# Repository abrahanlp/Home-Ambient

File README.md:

# Home-Ambient
 2-wire smart home thermostat with temperature, humidity, pressure and air quality measurements.

The main target is replace traditional tow wires bimetal thermostats with an intelligent one, cable to integrate with [HomeAssistance](https://www.home-assistant.io/) or works _standalone_ with custom firmware.

## 2-wire classical thermostat replacement

### Working principle
Images below explain graphically how this system works.

The main and mandatory system requirement is a big difference between Control an Load level power. While load is some orders of magnitud above, there should not be problem, but is mandatory review every case.

# Product Requirements

| Requirement   | Description  | Definition |
|:-------------:|:-------------|:----------:|
| Temperature	|  Temperature measurement, with minimal interference from the device.	| ±2°C 	|
| Humidity	| Humidity measurement from ambient 	| ±5% 	|
| Air quality	| Air quality estimation by particle detection| Not defined, optional |
| Switch	| 2 pole switch	| >=10A	|
| Switch feedback	| Switch feedback to check operation | Digital or analog |
| HA | Home Assistance integration	| Mandatory	|
| Display | Optional e-Ink display	| No power relevant|
| Autonomy | Capable to operate without power	| At least 2h |

## Hardware architecture
Home-Ambient block diagram is show on image below.

The PCB hardware distribution is proposed on next image.

### Power supply, SEPIC converter
Energy when the load is activated is provided by a battery. The voltage from this power source varies from above and below 3,3V, so it is neccesary _'boost'_ and _'buck'_ converter.
Here is where the SEPIC converter comes to action, capable of manage both situations at the same time.

### CPU
The easiest way to integrate custom electronics on _HomeAssistant_ are the [ESPHome](https://esphome.io/) devices. This smart thermostat will be designed around classical [ESP32-C3](https://www.espressif.com/en/products/socs/esp32-c3).

### Sensors and actuators
The BME680 air quality sensor covers all requirements. More info about this component can be found on [Bosch official website](https://www.bosch-sensortec.com/en/products/environmental-sensors/gas-sensors/bme680).

## Home Assistant integration
As said before, integration is done by [ESPHome](https://esphome.io/), there is no easier way to do this.

After integration on Home-Assistant, a schedule programmer is implemented using the [Niels Faber](https://github.com/nielsfaber) tools.

# More info on [FaultyProject](https://faultyproject.es/)
If you are interested how this project was developed take a look on the next links:
 1. [Introduction](https://faultyproject.es/proyectos/home-ambient/home-ambient-intro/)
 2. [Prototype](https://faultyproject.es/proyectos/home-ambient/home-ambient-prototipo/)
 3. [Schematichs & PCB Design](https://faultyproject.es/proyectos/home-ambient/home-ambient-hardware-esquema-y-pcb/)
 4. [Home Assistant Integration](https://faultyproject.es/proyectos/home-ambient/home-ambient-integracion-con-home-assistant-y-esphome/)
 5. Case design (Future work... )

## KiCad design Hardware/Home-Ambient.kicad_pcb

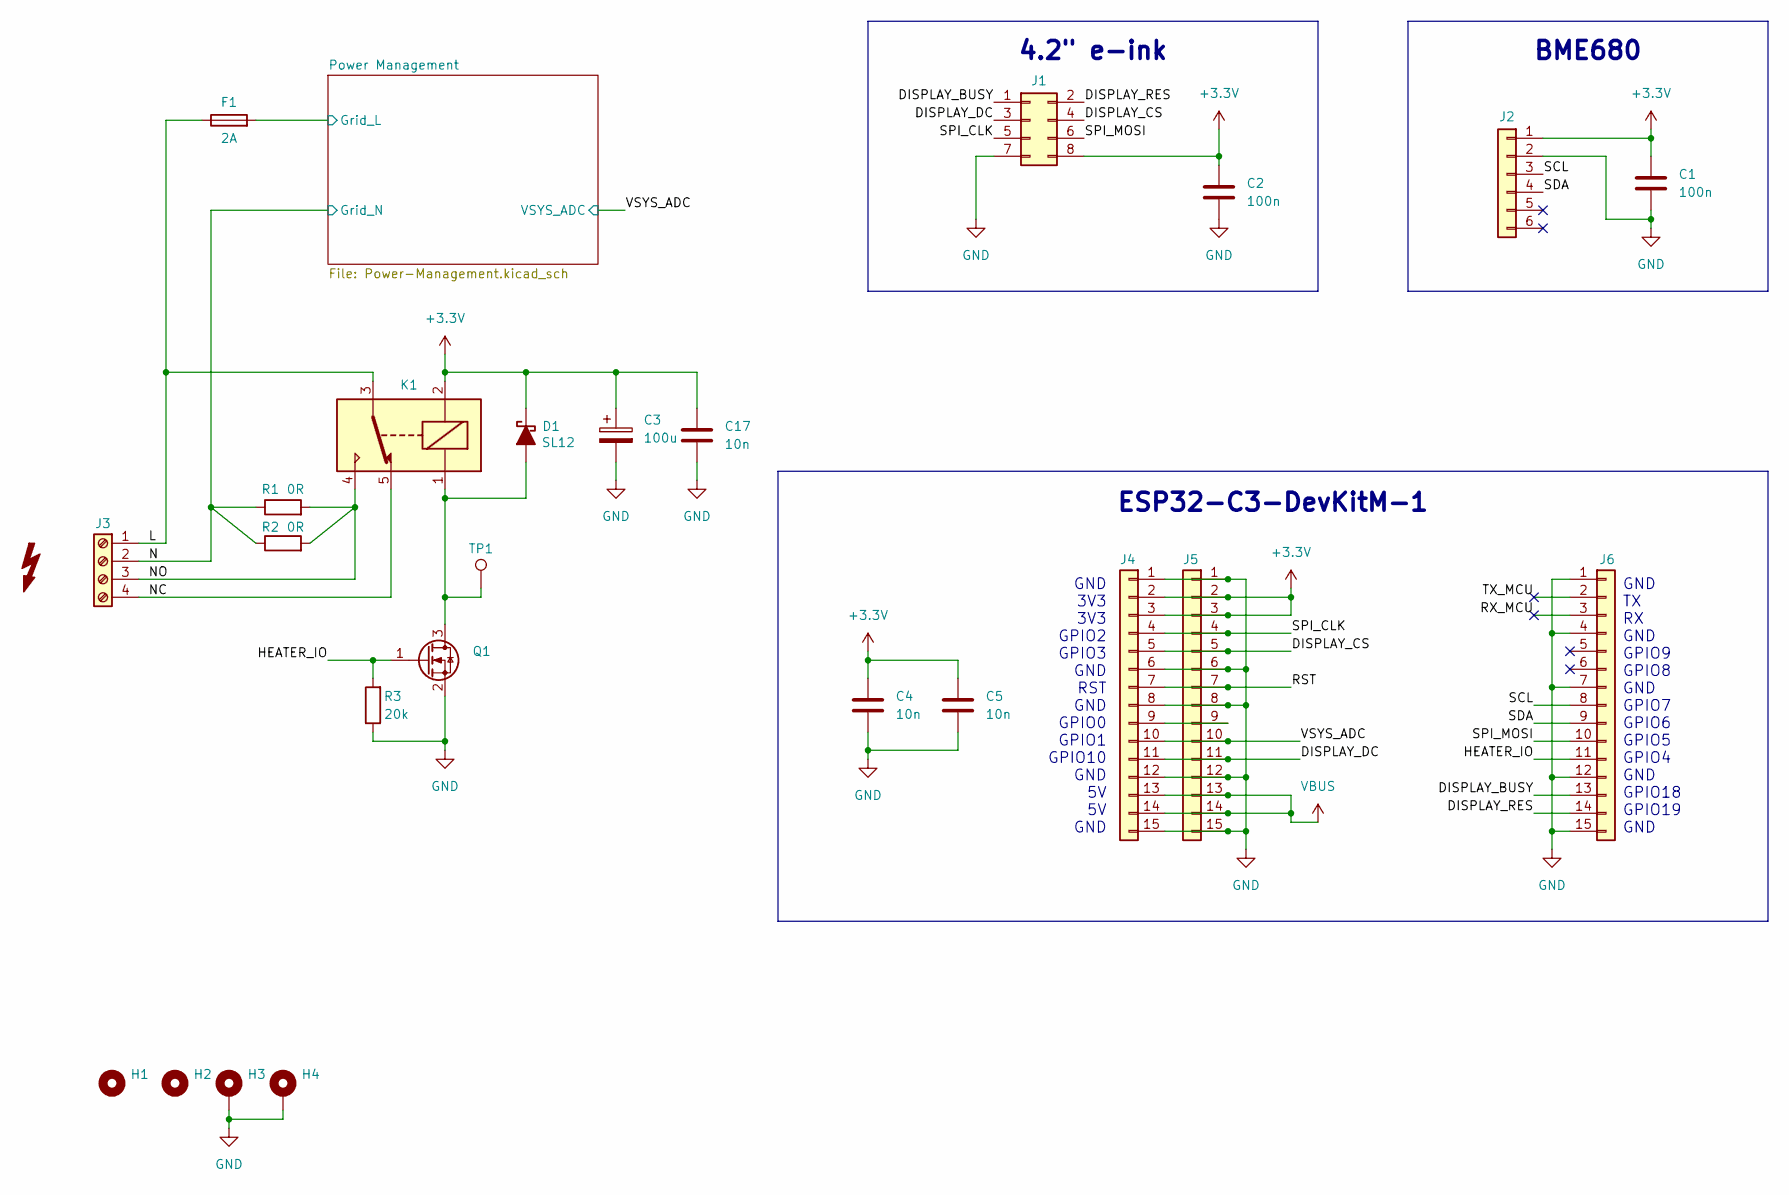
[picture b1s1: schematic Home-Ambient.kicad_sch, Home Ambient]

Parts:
C1, C2: 100n; C_1206_3216Metric_Pad1.33x1.80mm_HandSolder
C3: 100u; C_1210_3225Metric_Pad1.33x2.70mm_HandSolder
C4, C5, C17: 10n; C_1206_3216Metric_Pad1.33x1.80mm_HandSolder
D1: SL12; D_SMA_Handsoldering
F1: 2A; 0697H____
H1, H2: MountingHole; MountingHole_3.2mm_M3
H3, H4: MountingHole_Pad; MountingHole_3.2mm_M3_Pad_TopBottom
J1: Conn_02x05_Odd_Even; PinHeader_2x04_P2.54mm_Vertical
J2: Conn_01x06; PinHeader_1x06_P2.54mm_Vertical
J3: Screw_Terminal_01x04; TerminalBlock_Altech_AK300-4_P5.00mm
J4, J5, J6: Conn_01x15; PinHeader_1x15_P2.54mm_Vertical
K1: Relay_SPDT; J1071CS3VDC36
Q1: SSF2320Y; SOT-23_Handsoldering
R1, R2: 0R; R_1812_4532Metric_Pad1.30x3.40mm_HandSolder
R3: 20k; R_0805_2012Metric_Pad1.20x1.40mm_HandSolder
TP1: TestPoint_Pad_2.0x2.0mm

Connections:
+3.3V: C1.1, C2.1, C3.1, C4.1, C5.1, C17.1, D1.1 (K), J1.8, J2.1, J4.2, J4.3, J5.2, J5.3, K1.2; also elsewhere on the board
/DISPLAY_BUSY: J1.1, J6.13
/DISPLAY_CS: J1.4, J4.5, J5.5
/DISPLAY_DC: J1.3, J4.11, J5.11
/DISPLAY_RES: J1.2, J6.14
/HEATER_IO: J6.11, Q1.1 (G), R3.2
/L: F1.1, J3.1, K1.3
/N: J3.2, R1.1, R2.1; also elsewhere on the board
/NC: J3.4, K1.5
/NO: J3.3, K1.4, R1.2, R2.2
/Power Management/Grid_L: F1.2; also elsewhere on the board
/RST: J4.7, J5.7
/RX_MCU: J6.3
/SCL: J2.3, J6.8
/SDA: J2.4, J6.9
/SPI_CLK: J1.5, J4.4, J5.4
/SPI_MOSI: J1.6, J6.10
/TX_MCU: J6.2
/VSYS_ADC: J4.10, J5.10; also elsewhere on the board
GND: C1.2, C2.2, C3.2, C4.2, C5.2, C17.2, H3.1, H4.1, J1.7, J2.2, J4.1, J4.6, J4.8, J4.12, J4.15, J5.1, J5.6, J5.8, J5.12, J5.15, J6.1, J6.4, J6.7, J6.12, J6.15, Q1.2 (S), R3.1; also elsewhere on the board
unnamed: D1.2 (A), K1.1, Q1.3 (D), TP1.1
unnamed: J4.9, J5.9
VBUS: J4.13, J4.14, J5.13, J5.14

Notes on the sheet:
BME680
4.2" e-ink
GND TX RX GND GPIO9 GPIO8 GND GPIO7 GPIO6 GPIO5 GPIO4 GND GPIO18 GPIO19 GND
GND 3V3 3V3 GPIO2 GPIO3 GND RST GND GPIO0 GPIO1 GPIO10 GND 5V 5V GND
ESP32-C3-DevKitM-1

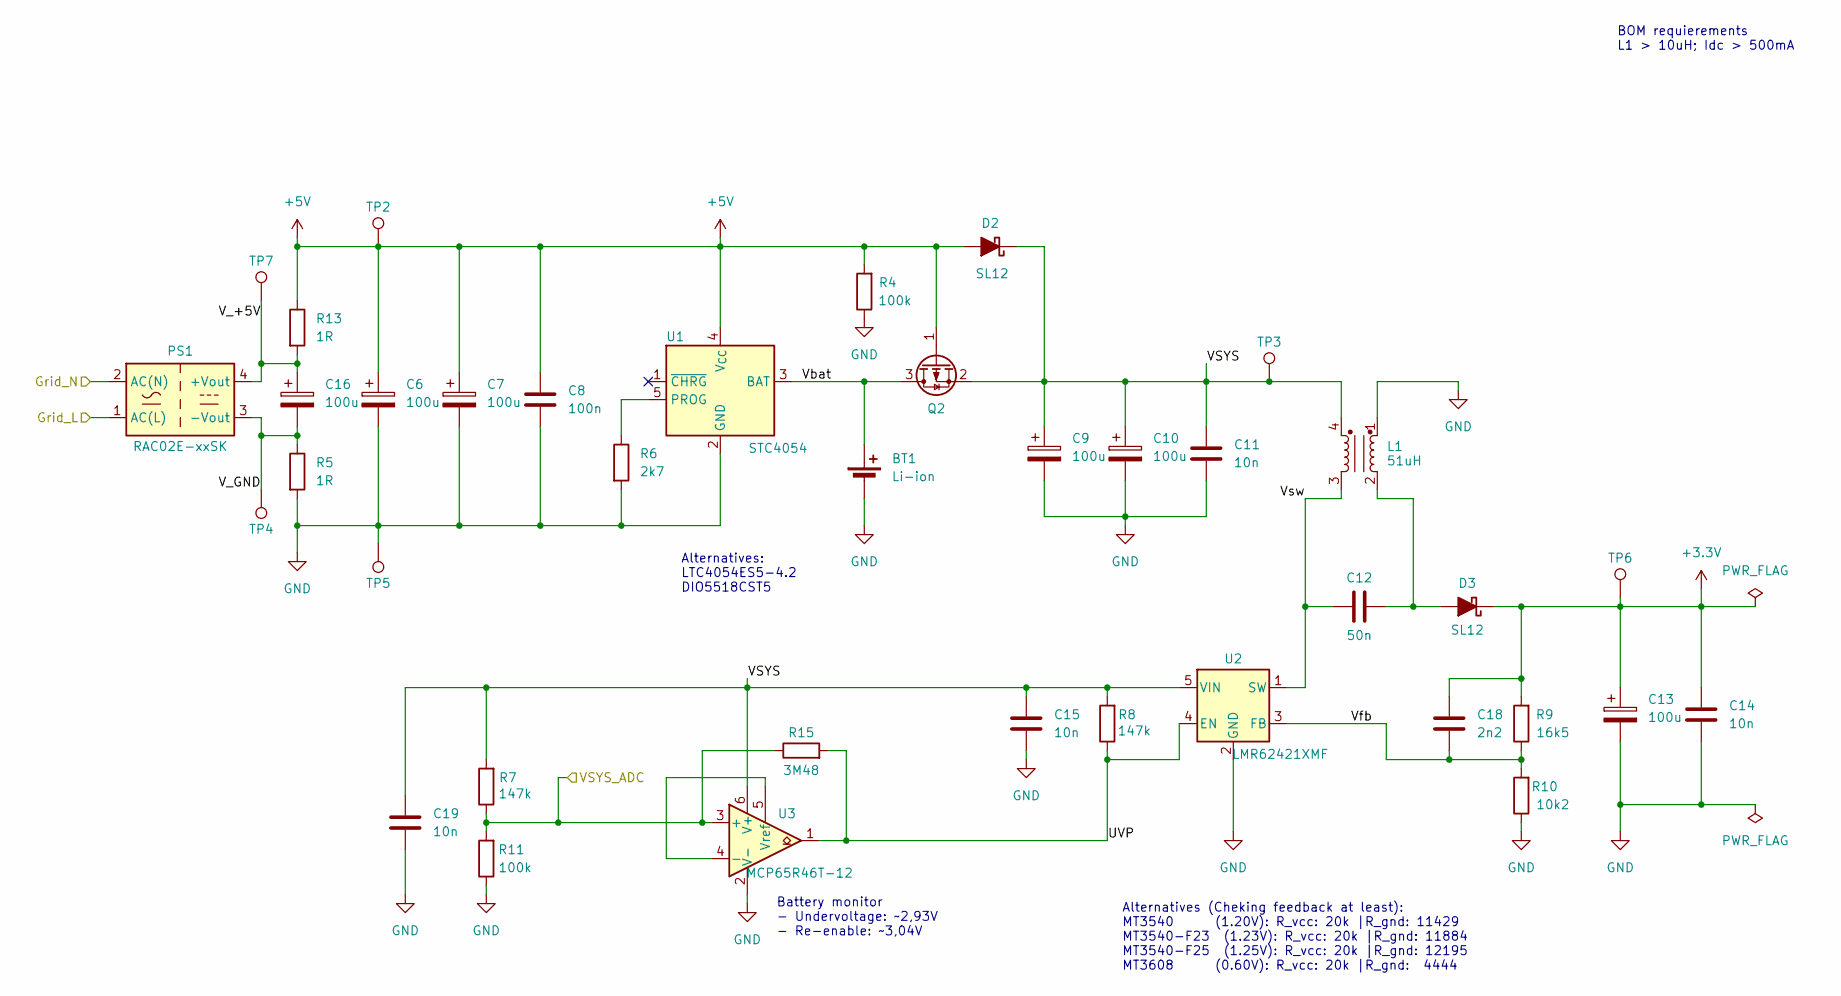
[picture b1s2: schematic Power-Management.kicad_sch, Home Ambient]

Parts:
BT1: Li-ion; Molex_SL_171971-0002_1x02_P2.54mm_Vertical
C6, C7, C9, C10, C13, C16: 100u; C_1210_3225Metric_Pad1.33x2.70mm_HandSolder
C8: 100n; C_1206_3216Metric_Pad1.33x1.80mm_HandSolder
C11, C14, C15, C19: 10n; C_1206_3216Metric_Pad1.33x1.80mm_HandSolder
C12: 50n; C_1206_3216Metric_Pad1.33x1.80mm_HandSolder
C18: 2n2; C_0805_2012Metric_Pad1.18x1.45mm_HandSolder
D2, D3: SL12; D_SMA_Handsoldering
L1: 51uH; Murata_5000A
PS1: RAC02E-xxSK; RAC02E-K
Q2: DMP31D1U-7; SOT-23_Handsoldering
R4, R11: 100k; R_0805_2012Metric_Pad1.20x1.40mm_HandSolder
R5, R13: 1R; R_1206_3216Metric_Pad1.30x1.75mm_HandSolder
R6: 2k7; R_0805_2012Metric_Pad1.20x1.40mm_HandSolder
R7, R8: 147k; R_0805_2012Metric_Pad1.20x1.40mm_HandSolder
R9: 16k5; R_0805_2012Metric_Pad1.20x1.40mm_HandSolder
R10: 10k2; R_0805_2012Metric_Pad1.20x1.40mm_HandSolder
R15: 3M48; R_0805_2012Metric_Pad1.20x1.40mm_HandSolder
TP2, TP3, TP4, TP5, TP6, TP7: TestPoint_Pad_2.0x2.0mm
U1: STC4054; TSOT-23-5_HandSoldering
U2: LMR62421XMF; SOT-23-5_HandSoldering
U3: MCP65R46T-12; SOT-23-6_Handsoldering

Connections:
+3.3V: C13.1, C14.1, C18.1, D3.1 (K), R9.2, TP6.1; also elsewhere on the board
+5V: C6.1, C7.1, C8.1, D2.2 (A), Q2.1 (G), R4.2, R13.1, TP2.1, U1.4 (V_{CC})
/N: PS1.2 (AC(N)); also elsewhere on the board
/Power Management/Grid_L: PS1.1 (AC(L)); also elsewhere on the board
/Power Management/UVP: R8.1, R15.2, U2.4 (EN), U3.1
/Power Management/VSYS: C9.1, C10.1, C11.1, C15.1, C19.1, D2.1 (K), L1.4, Q2.2 (S), R7.2, R8.2, TP3.1, U2.5 (VIN), U3.6 (V+)
/Power Management/V_+5V: C16.1, PS1.4 (+Vout), R13.2, TP7.1
/Power Management/V_GND: C16.2, PS1.3 (-Vout), R5.1, TP4.1
/Power Management/Vbat: BT1.1 (+), Q2.3 (D), U1.3 (BAT)
/Power Management/Vfb: C18.2, R9.1, R10.2, U2.3 (FB)
/Power Management/Vsw: C12.1, L1.3, U2.1 (SW)
/VSYS_ADC: R7.1, R11.2, R15.1, U3.3 (+); also elsewhere on the board
GND: BT1.2 (-), C6.2, C7.2, C8.2, C9.2, C10.2, C11.2, C13.2, C14.2, C15.2, C19.2, L1.1, R4.1, R5.2, R6.2, R10.1, R11.1, TP5.1, U1.2 (GND), U2.2 (GND), U3.2 (V-); also elsewhere on the board
unnamed: C12.2, D3.2 (A), L1.2
unnamed: R6.1, U1.5 (PROG)
unnamed: U3.4 (-), U3.5 (Vref)

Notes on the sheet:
Battery monitor - Undervoltage: ~2,93V - Re-enable: ~3,04V
Alternatives: LTC4054ES5-4.2 DIO5518CST5
Alternatives (Cheking feedback at least): MT3540 (1.20V): R_vcc: 20k |R_gnd: 11429 MT3540-F23 (1.23V): R_vcc: 20k |R_gnd: 11884 MT3540-F25 (1.25V): R_vcc: 20k |R_gnd: 12195 MT3608 (0.60V): R_vcc: 20k |R_gnd: 4444
BOM requierements L1 > 10uH; Idc > 500mA

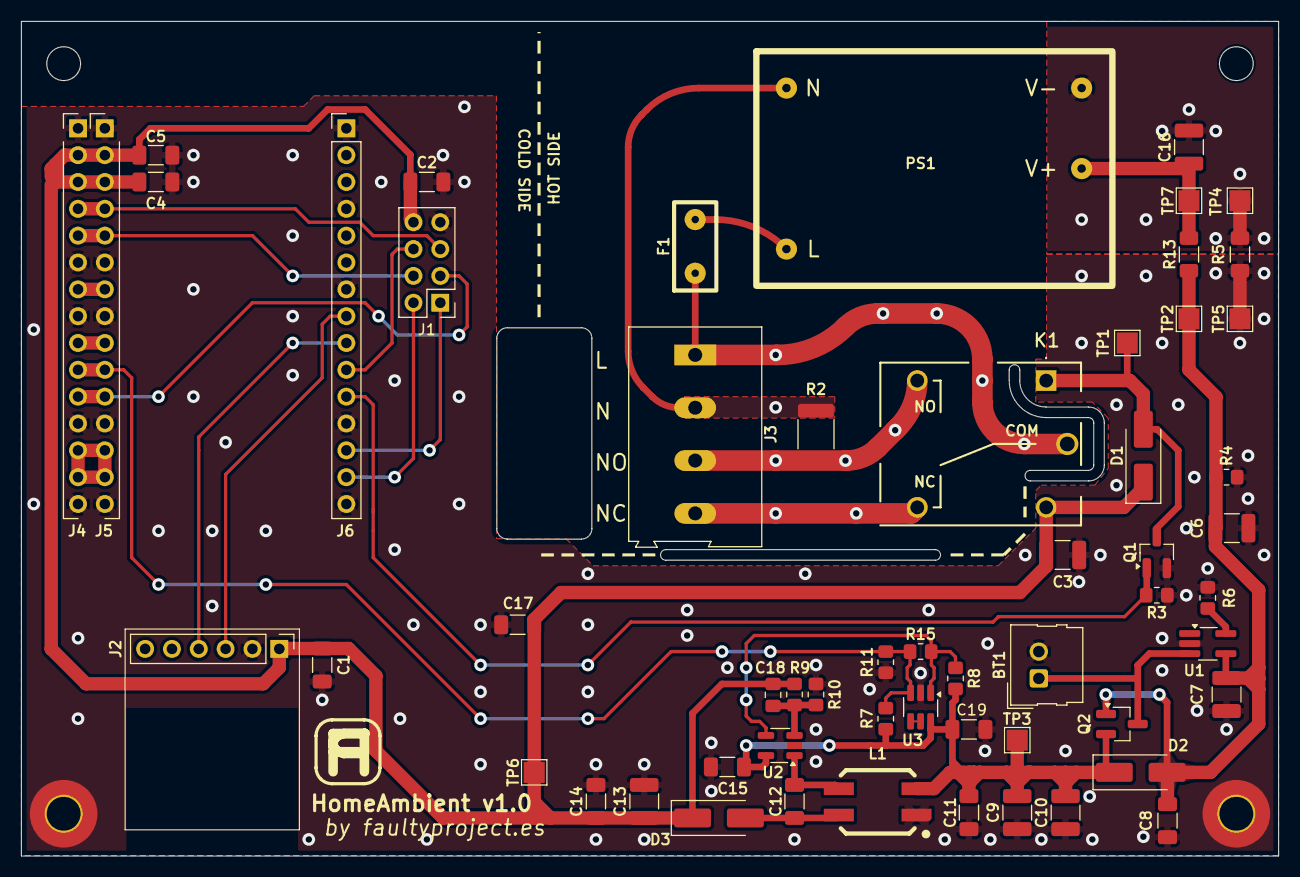
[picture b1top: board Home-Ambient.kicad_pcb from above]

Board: 2 copper layers, 119.0 x 79.0 mm, 62 parts (1 on the bottom side), 32 nets.

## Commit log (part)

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2024-09-13 More project info on README
2024-11-23 Basic Arduino hardware test
2024-12-19 Added YAML ESPHome file.
2025-01-03 Diagram added
2025-04-06 HW to KiCAD 9. Added library components
2025-04-14 RECOM footprint. Pinhead footprints.
2025-04-16 Updated sch.
2025-04-18 SEPIC script Octave.
2025-04-19 Basic SEPIC circuit for calculations. Li-ion charger.
2025-04-30 Basic SEPIC calculations.
2025-05-02 SEPIC first components value approach. SEPIC calculations corrections.
2025-05-03 FP Sheet. Voltage feedback and undervoltage detection.
2025-05-03 ESP32 connections
2025-05-04 Fixed R1 and R2 uv calculation. Current measure resistor en GND power source.
2025-05-30 Complete schematics
2025-05-31 Common mode inductor symbol, footprint
2025-06-01 Common mode footprint pin fix and silkscreen
2025-06-01 Symbol, footprint and 3D model relay
2025-06-03 BOM completed
2025-06-05 Added optional power source
2025-06-12 ZP05SXX00WB footprint
2025-06-15 Fuse and main connector footprints. ERC check.
2025-07-03 Moved SEPIC controller supply from battery to power commuter.
2025-07-04 PCB progress
2025-07-06 New 100uF capacitor package.
2025-07-20 PCB delimitation. Optional 5V Power supply removed because size constraint.
2025-08-07 Mounting holes and PCB progress.
2025-08-08 Fixed references. Parallel resistor on thermostat connection config.
2025-08-10 Equalizing output power supply impedance.
2025-08-10 PCB Progress.
2025-08-12 Grounding pending. DRU file added.
2025-08-13 Ground planes
2025-08-13 Crossing tracks on 90 degrees. Rework on Grid Power tracks
2025-08-13 Replaced main and battery supply switch transistor reference.
2025-08-13 First PCB draft finished.
2025-08-13 Vias placing. 10nF added on 3V relay PDN
2025-08-13 Vias refinement.
2025-08-13 Warning and instrucction silkscreens.
2025-08-14 Add and set 3D models.
2025-08-15 Basic 3D files.
2025-08-16 Added PCB dimmensions
2025-08-16 Case progress
2025-08-17 Enclosure main parts finished.
2025-08-17 Removed soldermask over power tracks. Relay footprint edit for silkscreen margin.
2025-08-29 BOM updated, SEPIC regulator replaced.
2025-08-29 SEPIC footprint fixed.
2025-09-02 Added battery undervoltage circuit.
2025-09-04 Comparator simulation
2025-09-06 Schematic and BOM updated with new undervoltage protection.
2025-09-07 Closed PCB layout
2025-09-07 Check DRU
2025-09-14 Docu diagram update
2025-09-17 Final BOM
2025-09-21 Production files
2025-09-28 Documentation
2025-11-12 Docu update. GPIO0 ADC removed on yaml file
2025-11-25 Voltage system gain and unit update.
2026-01-09 Bottom case
2026-01-11 Basic case
2026-01-11 Display hole
2026-01-14 PCB holder height
2026-01-15 Added fix mounting part
2026-01-15 Fix part names
2026-01-15 PCB mounting hole
2026-01-16 M2.5 Nut hole
2026-01-18 Bottom nuts pattern and display height
2026-01-18 Mounting holes on top part
2026-01-21 RGB turn on red on heat_action
2026-01-21 BOM. Increased SEPIC output from 3,285 to 3,326.
2026-01-27 Test Arduino sketch modified to last hardware. - Removing UV sensor - Adding redundant temperature sensor - BMS voltaje now is system voltaje
2026-01-27 SEPIC Octave script moved to hardware. Added SEPIC test with choke inductor
2026-01-27 Test file name fix
2026-01-28 RGB can be turned off by Serial.
2026-02-20 SEPIC LTSpice model.
2026-03-01 Increased venting holes size and increased by one.
2026-03-01 Added display place helper
2026-03-05 Update notes about SEPIC feedback resistors.
2026-03-06 README update before opening the repo
2026-03-06 Add GNU AGPL v3 license
    Project under GNU Affero General Public License version 3
